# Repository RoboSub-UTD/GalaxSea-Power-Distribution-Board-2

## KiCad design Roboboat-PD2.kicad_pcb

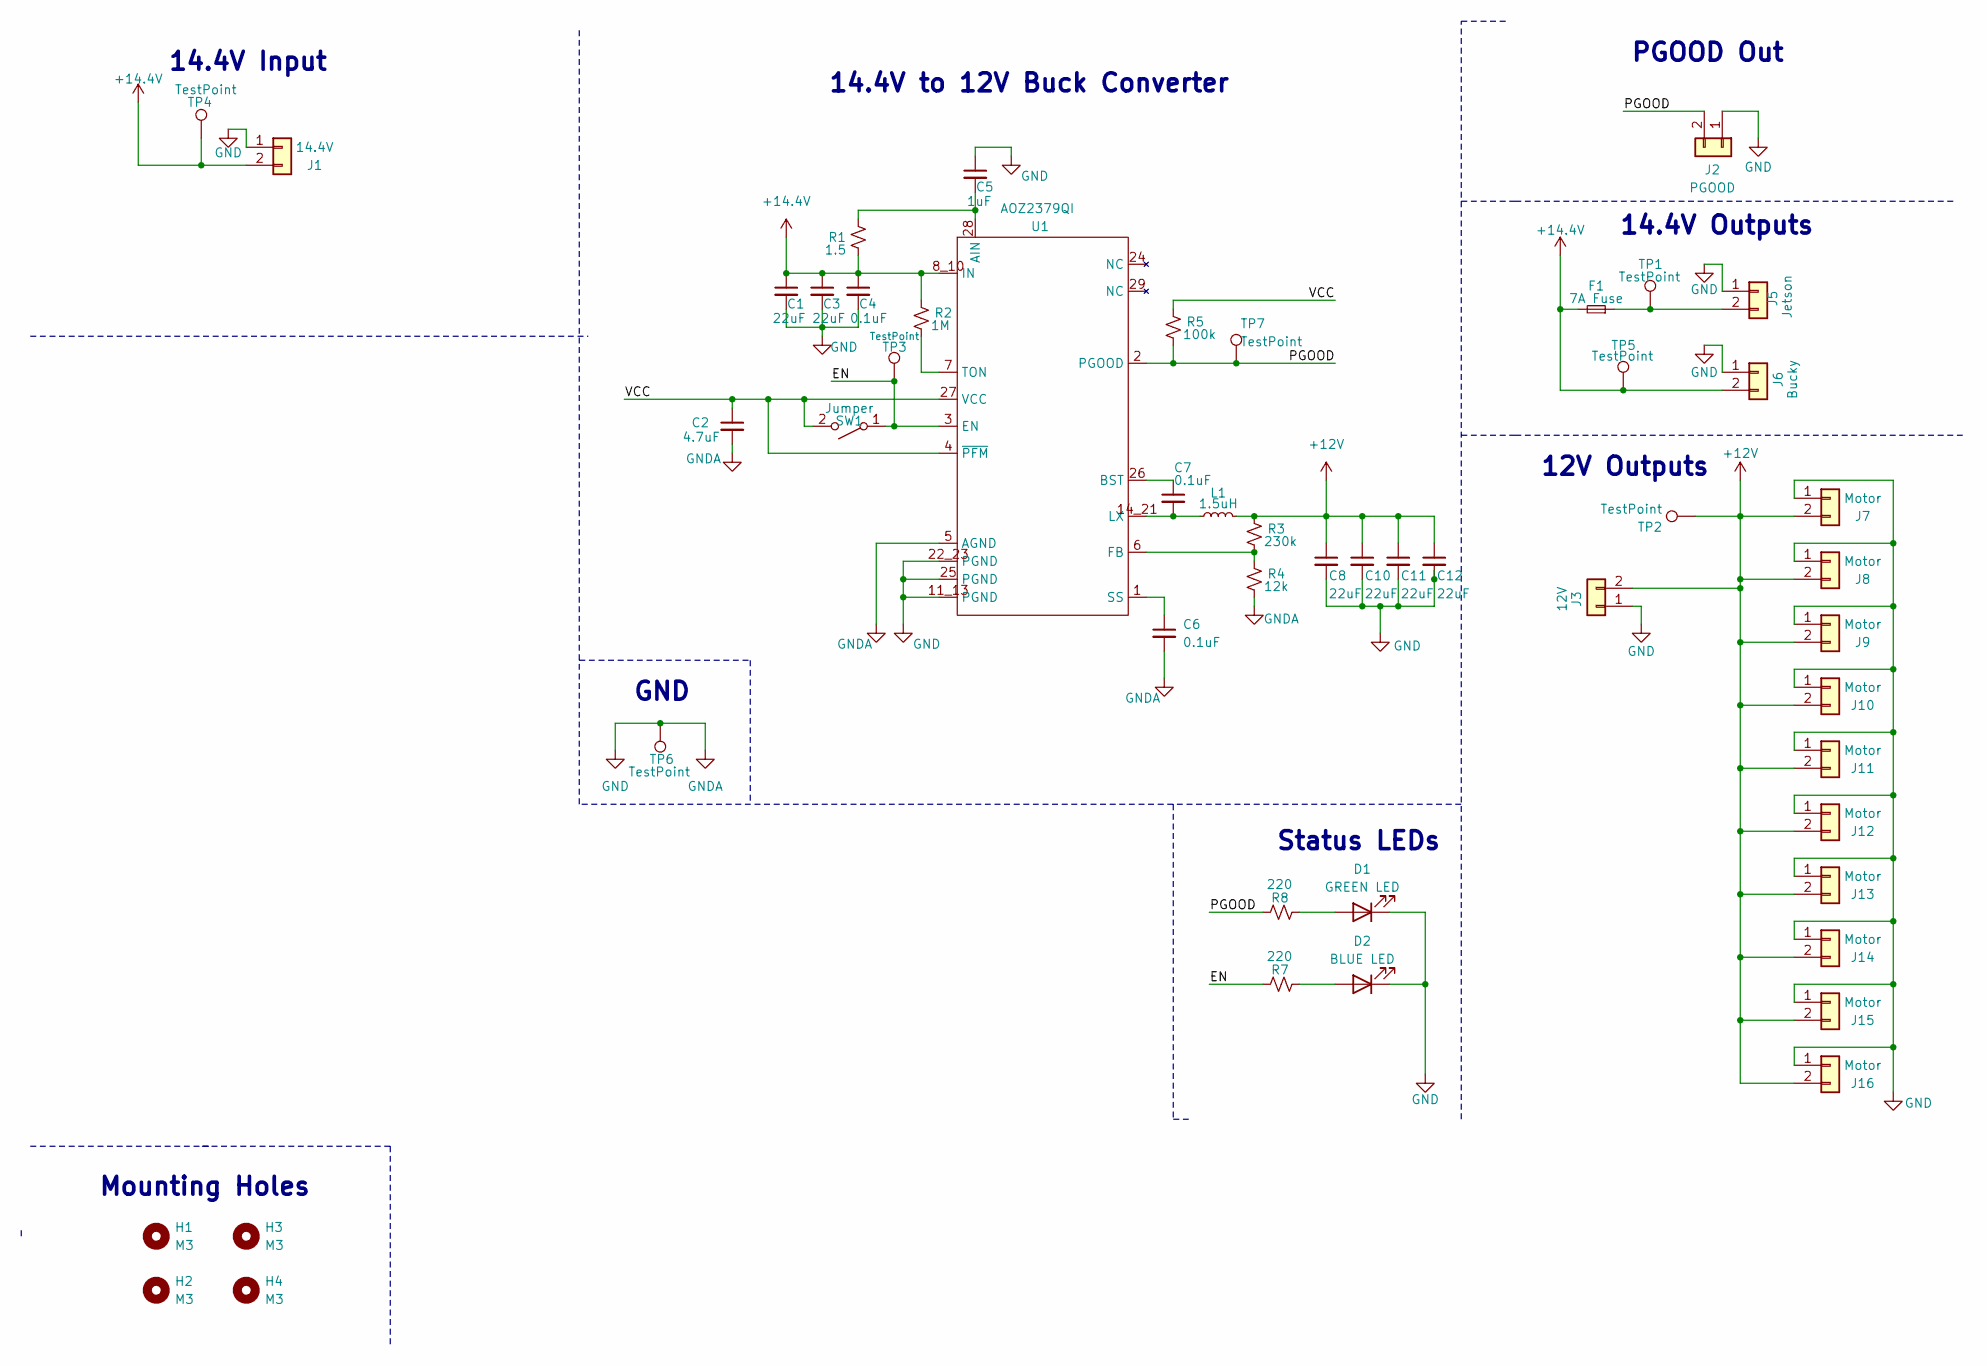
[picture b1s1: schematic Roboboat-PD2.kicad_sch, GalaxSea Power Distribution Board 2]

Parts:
C1, C3, C8, C10, C11, C12: 22uF; C_0805_2012Metric
C2: 4.7uF; C_0805_2012Metric
C4, C6, C7: 0.1uF; C_0805_2012Metric
C5: 1uF; C_0805_2012Metric
D1: GREEN LED; LED_D5.0mm
D2: BLUE LED; LED_D5.0mm
F1: 7A Fuse; Fuse_1206_3216Metric
H1, H2, H3, H4: M3; MountingHole_3.2mm_M3
J1: 14.4V; XT90_V
J2: PGOOD; JST_VH_B2P-VH-B_1x02_P3.96mm_Vertical
J3: 12V; AMASS_XT60-M_1x02_P7.20mm_Vertical
J5: Jetson; AMASS_XT60-M_1x02_P7.20mm_Vertical
J6: Bucky; AMASS_XT60-M_1x02_P7.20mm_Vertical
J7, J8, J9, J10, J11, J12, J13, J14, J15, J16: Motor; JST_VH_B2P-VH-B_1x02_P3.96mm_Vertical
L1: 1.5uH; IND_SRP1265A-1R5M
R1: 1.5; R_0805_2012Metric
R2: 1M; R_0805_2012Metric
R3: 230k; R_0805_2012Metric
R4: 12k; R_0805_2012Metric
R5: 100k; R_0805_2012Metric
R7, R8: 220; R_0805_2012Metric
SW1: Jumper; PinHeader_1x02_P2.54mm_Vertical
TP1, TP2, TP3, TP4, TP5, TP6, TP7: TestPoint; TestPoint_Keystone_5000-5004_Miniature
U1: AOZ2379QI; AOZ2369QI-11

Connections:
+12V: C8.1, C10.1, C11.1, C12.1, J3.2, J7.2, J8.2, J9.2, J10.2, J11.2, J12.2, J13.2, J14.2, J15.2, J16.2, L1.2, R3.1, TP2.1
+14.4V: C1.1, C3.1, C4.1, F1.2, J1.2, J6.2, R1.2, R2.1, TP4.1, TP5.1, U1.8_10 (IN)
/EN: R7.2, SW1.1 (A), TP3.1, U1.3 (EN)
/PGOOD: J2.2, R5.2, R8.2, TP7.1, U1.2 (PGOOD)
/VCC: C2.1, R5.1, SW1.2 (B), U1.4 (~PFM), U1.27 (VCC)
GND: C1.2, C2.2, C3.2, C4.2, C5.1, C6.2, C8.2, C10.2, C11.2, C12.2, D1.1 (K), D2.1 (K), J1.1, J2.1, J3.1, J5.1, J6.1, J7.1, J8.1, J9.1, J10.1, J11.1, J12.1, J13.1, J14.1, J15.1, J16.1, R4.2, TP6.1, U1.5 (AGND), U1.11_13 (PGND), U1.22_23 (PGND), U1.25 (PGND)
unnamed: D1.2 (A), R8.1
unnamed: D2.2 (A), R7.1
unnamed: F1.1, J5.2, TP1.1
unnamed: C5.2, R1.1, U1.28 (AIN)
unnamed: C7.1, U1.26 (BST)
unnamed: R3.2, R4.1, U1.6 (FB)
unnamed: C7.2, L1.1, U1.14_21 (LX)
unnamed: C6.1, U1.1 (SS)
unnamed: R2.2, U1.7 (TON)

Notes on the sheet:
14.4V Outputs
GND
PGOOD Out
Status LEDs
12V Outputs
14.4V to 12V Buck Converter
14.4V Input
Mounting Holes

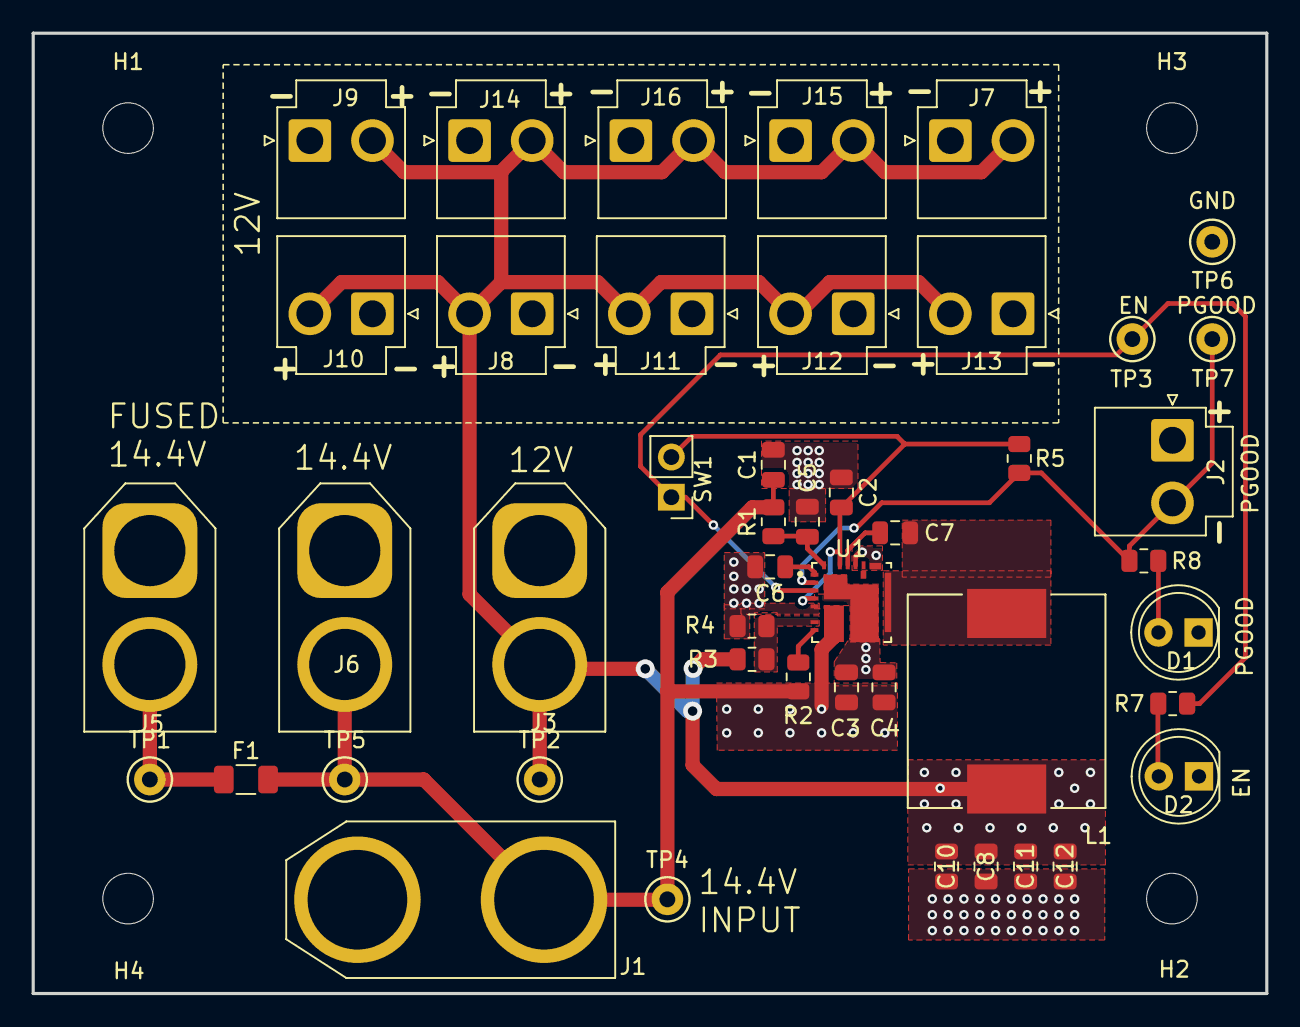
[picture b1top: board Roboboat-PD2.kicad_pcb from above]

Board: 2 copper layers, 78.0 x 60.7 mm, 50 parts (0 on the bottom side), 15 nets.

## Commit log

2024-12-22 clean up schematic
2024-12-22 finish schematic rough draft
2024-12-23 begin PCB layout
2024-12-27 finalize initial PCB draft
2025-01-03 Connect AGND to GND
2025-01-04 remove barrel connector
2025-01-04 add logo and board name
2025-01-04 rearrange bucky VIN loop
2025-01-04 add JLCPCB design rules
2025-01-04 rotate inductor
2025-01-04 fix screwholes, edge cuts, and GND plane
2025-01-05 rotate motor connectors
2025-01-05 make pretty
2025-01-05 fix mounting holes again
2025-01-05 fill zones
2025-01-05 move fuse
2025-01-05 fix footprints
2025-01-05 make DRC happy & rearrange stuff
2025-01-06 change fuse
2025-01-07 fix capacitor and resistor values and sizes
2025-01-07 tweak silkscreen
2025-01-07 tie PFM high, break out PGOOD
2025-01-08 rearrange board
2025-01-08 add PGOOD test points
2025-01-08 final touches
2025-01-09 add 0.1uF capacitor to PGOOD
2025-01-17 move R1, R2, R3, correct fuse footprint
2025-01-17 add mounting holes and test points to schematic
2025-01-17 add ground to PGOOD output
2025-01-18 begin switch to AOZ2379QI
2025-01-18 rearrange schematic
2025-01-18 hesitant buck converter circuit values
2025-01-19 correct XT-90 footprints
2025-01-19 add 0.1uF capacitors to PGOOD output
2025-01-19 redo PCB layout
2025-01-19 better silkscreens
2025-01-19 replace traces with fills
2025-01-20 add pullup resistor to PGOOD
2025-01-20 add status LEDs
2025-01-20 add more test points
2025-01-20 put SW1 on the correct side of the board
2025-01-21 correct buck converter component values
2025-01-21 make power traces thicker
2025-01-22 add GalaxSea logo
2025-01-23 rotate SW1
2025-01-23 move SW1
2025-01-23 add thermal pours
2025-01-23 add thermal vias
2025-01-24 use less thermal vias
2025-01-24 adjust VCC traces
2025-01-26 fix R_TON value
2025-01-26 give each LED its own resistor
2025-01-26 fix AIN resistor value
2025-01-26 remove 0.1uF capacitor from PGOOD
2025-01-26 remove test point section from schematic
2025-01-26 use test point symbol, wire PFM to VCC
2025-01-26 rename PFM to ~{PFM}
2025-01-26 move PGOOD test point
2025-01-27 fix AOZ2379QI symbol
2025-01-31 minor fixes and tweaks
2025-02-08 add 3D models
2025-02-08 make GND pins more clear and consistant
